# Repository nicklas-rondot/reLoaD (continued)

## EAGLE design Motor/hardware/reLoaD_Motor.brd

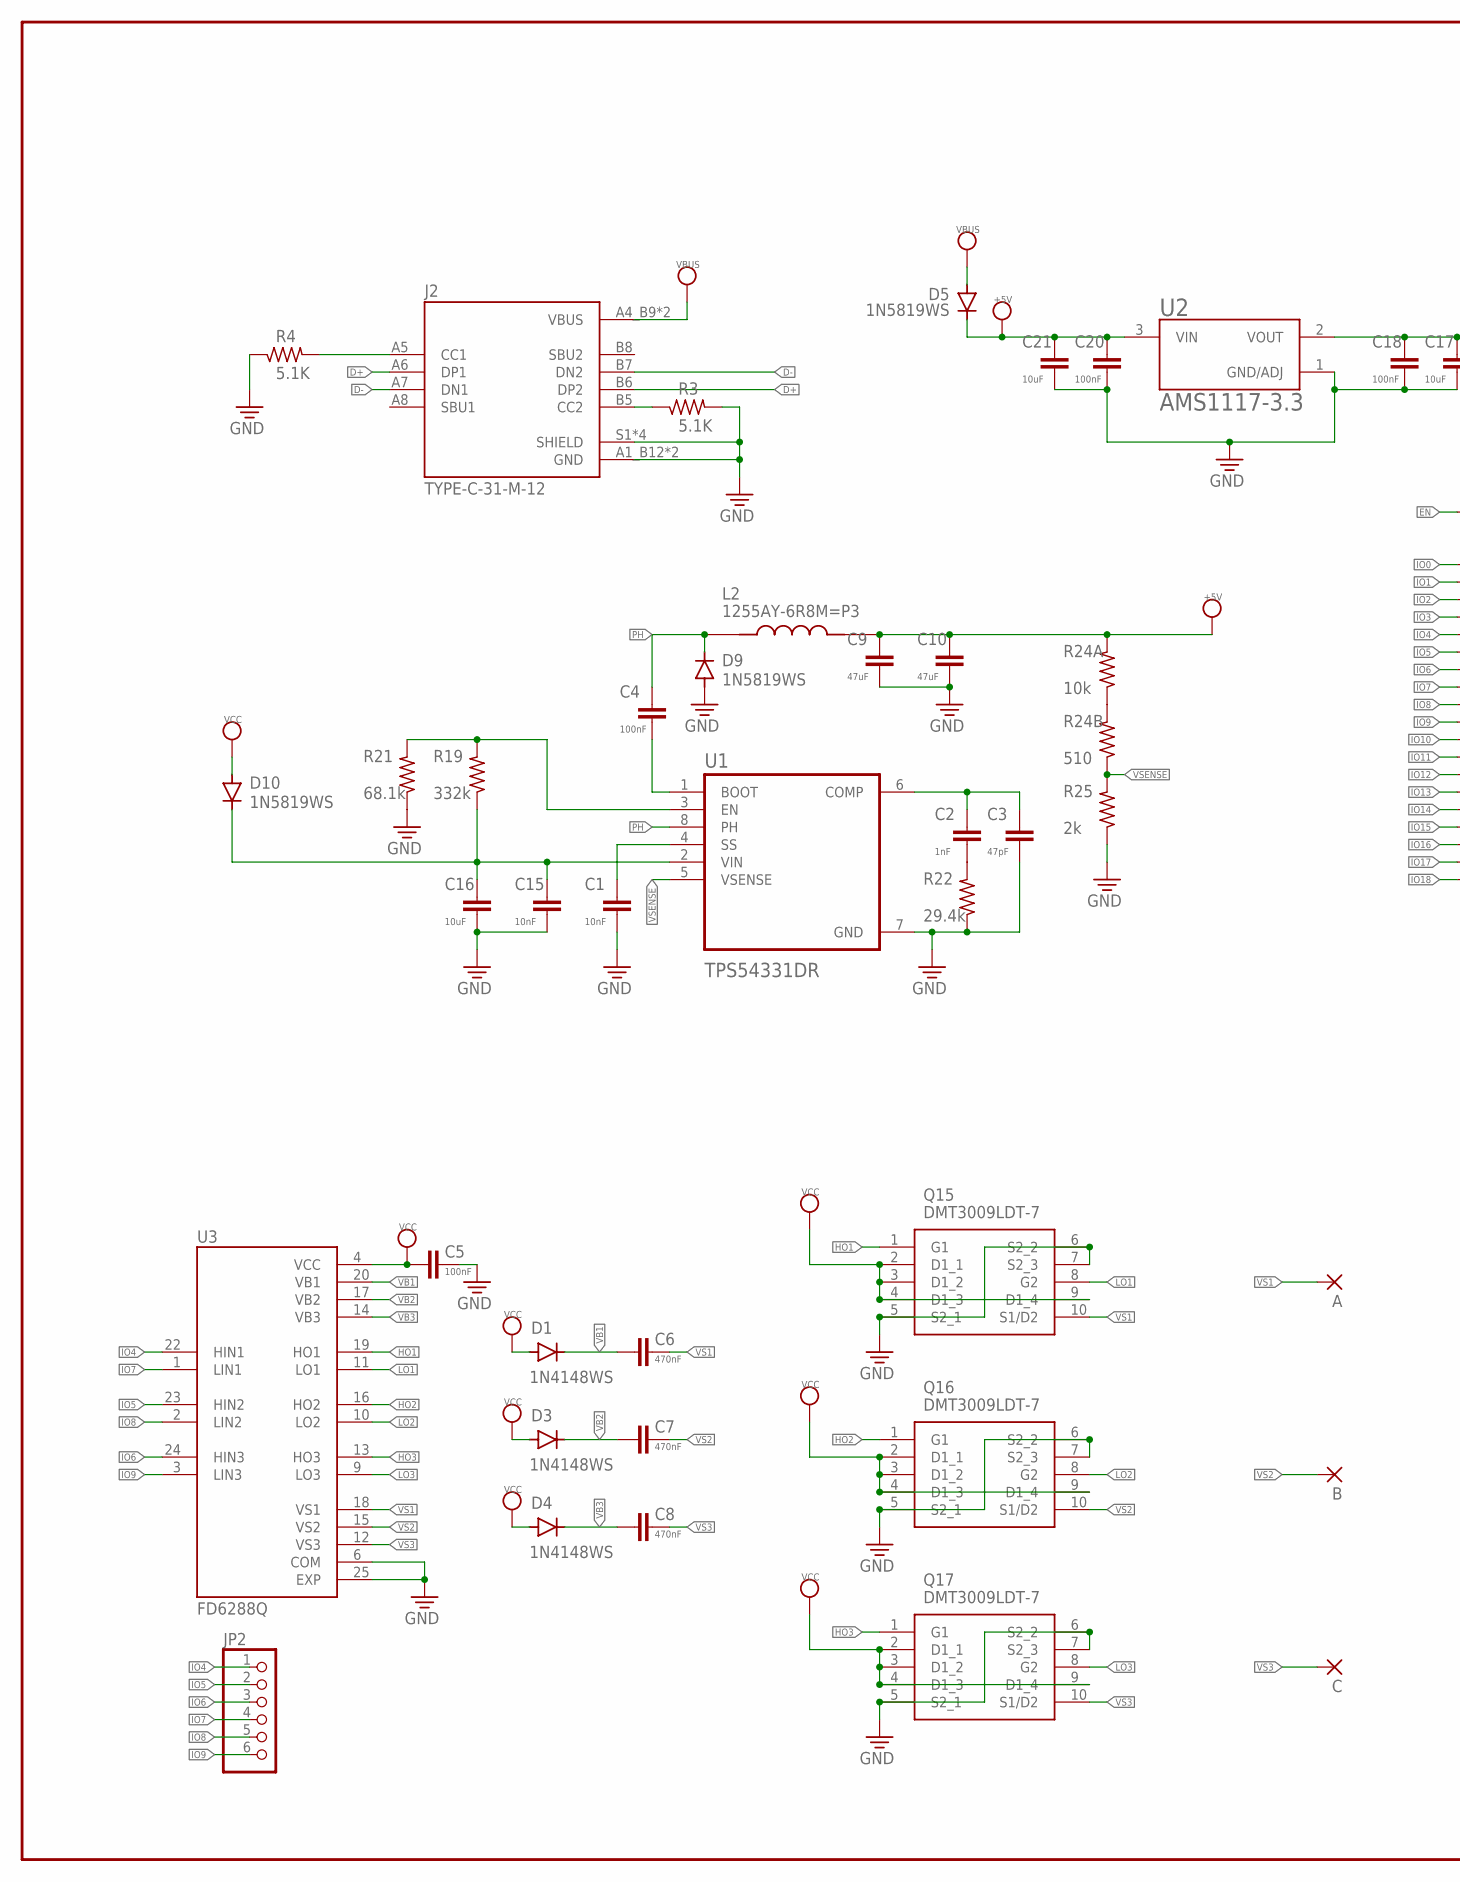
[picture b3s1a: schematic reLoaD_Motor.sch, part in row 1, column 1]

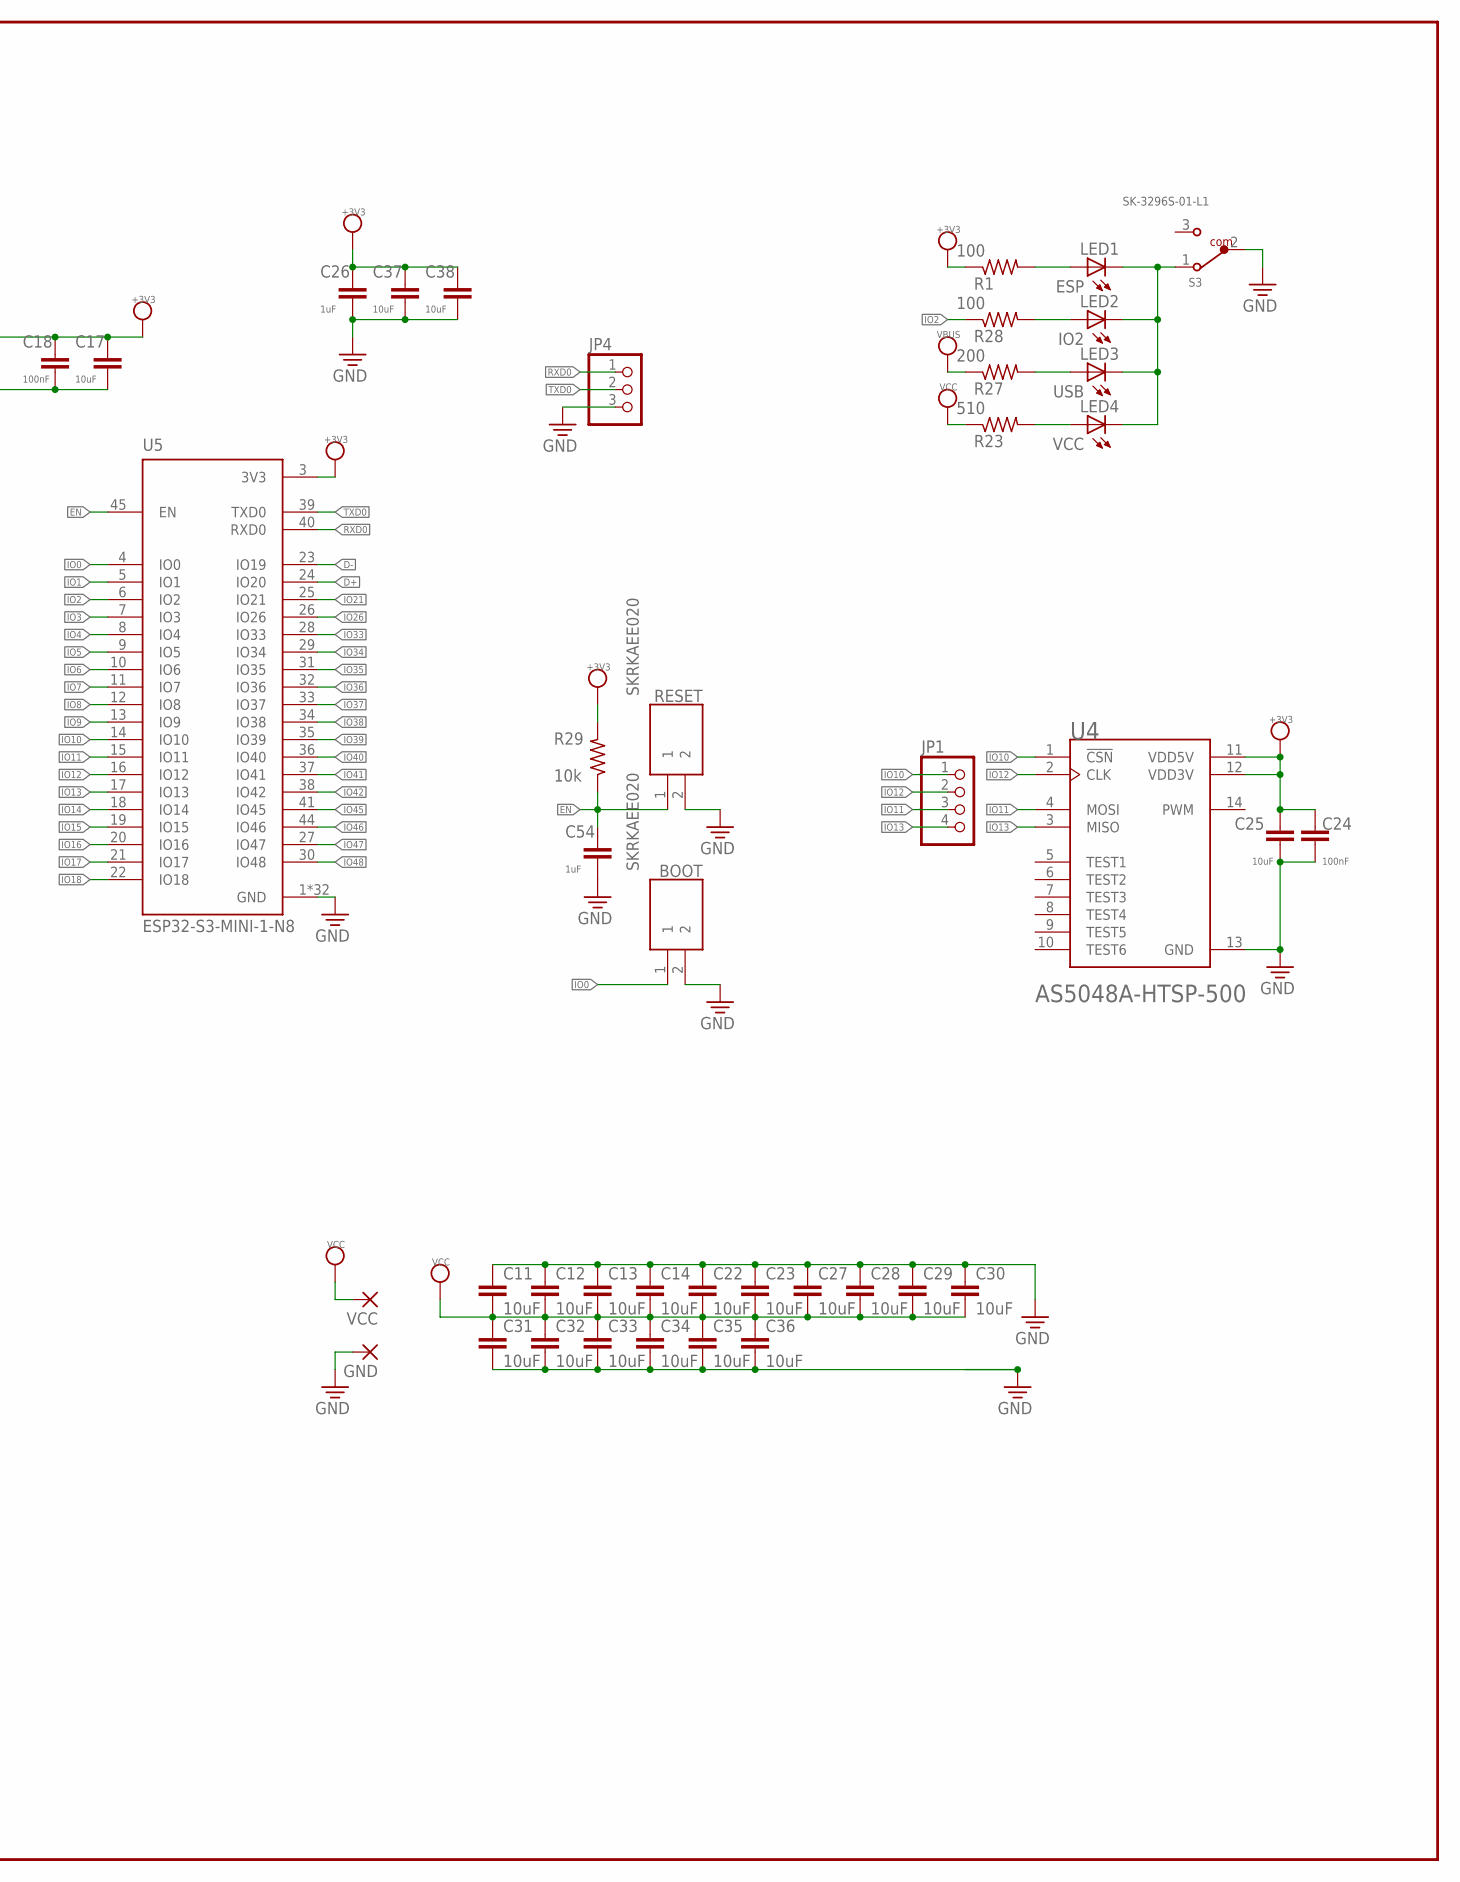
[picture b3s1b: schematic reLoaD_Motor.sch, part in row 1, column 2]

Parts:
A: 3,81/1,4
B: 3,81/1,4
BOOT: SKRKAEE020
C: 3,81/1,4
C1, C15: 10nF; C0603K
C2: 1nF; C0603K
C3: 47pF; C0603K
C4, C5, C18, C20, C24: 100nF; C0603K
C6, C7, C8: 470nF; C0603K
C9, C10: 47uF; C0603K
C11, C12, C13, C14, C22, C23, C27, C28, C29, C30, C31, C32, C33, C34, C35, C36: 10uF; C0805K
C16, C17, C21, C25, C37, C38: 10uF; C0603K
C26, C54: 1uF; C0603K
D1, D3, D4: 1N4148WS; SOD-323
D5, D9, D10: 1N5819WS; SOD323-W
GND: 3,81/1,4
J2: TYPE-C-31-M-12; HRO_TYPE-C-31-M-12
JP1: PINHD-1X4; 1X04
JP2: PINHD-1X6; 1X06
JP4: PINHD-1X3; 1X03
L2: 1255AY-6R8M=P3; IND_1255AY-6R8M=P3
LED1: ESP; CHIPLED_0805
LED2: IO2; CHIPLED_0805
LED3: USB; CHIPLED_0805
LED4: VCC; CHIPLED_0805
Q15, Q16, Q17: DMT3009LDT-7; DMT3009LDT7
R1, R28: 100; R0603
R3, R4: 5.1K; R0603
R19: 332k; R0603
R21: 68.1k; R0603
R22: 29.4k; R0603
R23, R24B: 510; R0603
R24A, R29: 10k; R0603
R25: 2k; R0603
R27: 200; R0603
RESET: SKRKAEE020
S3: SK-3296S-01-L1; 450404015514
U1: TPS54331DR; SOIC127P599X175-8N
U2: AMS1117-3.3; SOT229P700X180-4N
U3: FD6288Q; QFN50P400X400X90-25N
U4: AS5048A-HTSP-500; SOP65P640X120-14N
U5: ESP32-S3-MINI-1-N8; XCVR_ESP32-S3-MINI-1-N8
VCC: 3,81/1,4

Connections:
+3V3: C17.1, C18.1, C24.2, C25.2, C26.1, C37.1, C38.1, R1.1, R29.2, U2.2 (VOUT), U4.11 (VDD5V), U4.12 (VDD3V), U5.3 (3V3)
+5V: C9.1, C10.1, C20.1, C21.1, D5.C, L2.2, R24A.2, U2.3 (VIN)
D+: J2.A6 (DP1), J2.B6 (DP2), U5.24 (IO20)
D-: J2.A7 (DN1), J2.B7 (DN2), U5.23 (IO19)
EN: C54.1, R29.1, RESET.1, U5.45 (EN)
GND: BOOT.2, C1.2, C3.2, C5.1, C9.2, C10.2, C11.1, C12.1, C13.1, C14.1, C15.2, C16.2, C17.2, C18.2, C20.2, C21.2, C22.1, C23.1, C24.1, C25.1, C26.2, C27.1, C28.1, C29.1, C30.1, C31.2, C32.2, C33.2, C34.2, C35.2, C36.2, C37.2, C38.2, C54.2, D9.A, GND.1, J2.A1_B12 (GND), J2.B1_A12 (GND), J2.S1 (SHIELD), J2.S2 (SHIELD), J2.S3 (SHIELD), J2.S4 (SHIELD), JP4.3, Q15.5 (S2_1), Q15.6 (S2_2), Q15.7 (S2_3), Q16.5 (S2_1), Q16.6 (S2_2), Q16.7 (S2_3), Q17.5 (S2_1), Q17.6 (S2_2), Q17.7 (S2_3), R3.2, R4.1, R21.1, R22.1, R25.1, RESET.2, S3.2, U1.7 (GND), U2.1 (GND/ADJ), U3.6 (COM), U3.25 (EXP), U4.13 (GND), U5.1 (GND), U5.2 (GND), U5.42 (GND), U5.43 (GND), U5.46 (GND), U5.47 (GND), U5.48 (GND), U5.49 (GND), U5.50 (GND), U5.51 (GND), U5.52 (GND), U5.53 (GND), U5.54 (GND), U5.55 (GND), U5.56 (GND), U5.57 (GND), U5.58 (GND), U5.59 (GND), U5.60 (GND), U5.61 (GND), U5.61_1 (GND), U5.61_2 (GND), U5.61_3 (GND), U5.61_4 (GND), U5.61_5 (GND), U5.61_6 (GND), U5.61_7 (GND), U5.61_8 (GND), U5.62 (GND), U5.63 (GND), U5.64 (GND), U5.65 (GND)
HO1: Q15.1 (G1), U3.19 (HO1)
HO2: Q16.1 (G1), U3.16 (HO2)
HO3: Q17.1 (G1), U3.13 (HO3)
IO0: BOOT.1, U5.4 (IO0)
IO1: U5.5 (IO1)
IO2: R28.1, U5.6 (IO2)
IO3: U5.7 (IO3)
IO4: JP2.1, U3.22 (HIN1), U5.8 (IO4)
IO5: JP2.2, U3.23 (HIN2), U5.9 (IO5)
IO6: JP2.3, U3.24 (HIN3), U5.10 (IO6)
IO7: JP2.4, U3.1 (LIN1), U5.11 (IO7)
IO8: JP2.5, U3.2 (LIN2), U5.12 (IO8)
IO9: JP2.6, U3.3 (LIN3), U5.13 (IO9)
IO10: JP1.1, U4.1 (!CSN), U5.14 (IO10)
IO11: JP1.3, U4.4 (MOSI), U5.15 (IO11)
IO12: JP1.2, U4.2 (CLK), U5.16 (IO12)
IO13: JP1.4, U4.3 (MISO), U5.17 (IO13)
IO14: U5.18 (IO14)
IO15: U5.19 (IO15)
IO16: U5.20 (IO16)
IO17: U5.21 (IO17)
IO18: U5.22 (IO18)
IO21: U5.25 (IO21)
IO26: U5.26 (IO26)
IO33: U5.28 (IO33)
IO34: U5.29 (IO34)
IO35: U5.31 (IO35)
IO36: U5.32 (IO36)
IO37: U5.33 (IO37)
IO38: U5.34 (IO38)
IO39: U5.35 (IO39)
IO40: U5.36 (IO40)
IO41: U5.37 (IO41)
IO42: U5.38 (IO42)
IO45: U5.41 (IO45)
IO46: U5.44 (IO46)
IO47: U5.27 (IO47)
IO48: U5.30 (IO48)
LO1: Q15.8 (G2), U3.11 (LO1)
LO2: Q16.8 (G2), U3.10 (LO2)
LO3: Q17.8 (G2), U3.9 (LO3)
unnamed: LED3.A, R27.2
unnamed: LED4.A, R23.2
unnamed: LED1.A, R1.2
unnamed: J2.B5 (CC2), R3.1
unnamed: LED1.C, LED2.C, LED3.C, LED4.C, S3.1
unnamed: LED2.A, R28.2
unnamed: R19.2, R21.2, U1.3 (EN)
unnamed: C1.1, U1.4 (SS)
unnamed: R24A.1, R24B.2
unnamed: C2.1, C3.1, U1.6 (COMP)
unnamed: C2.2, R22.2
unnamed: C4.2, U1.1 (BOOT)
unnamed: C15.1, C16.1, D10.C, R19.1, U1.2 (VIN)
unnamed: J2.A5 (CC1), R4.2
PH: C4.1, D9.C, L2.1, U1.8 (PH)
RXD0: JP4.1, U5.40 (RXD0)
TXD0: JP4.2, U5.39 (TXD0)
VB1: C6.1, D1.C, U3.20 (VB1)
VB2: C7.1, D3.C, U3.17 (VB2)
VB3: C8.1, D4.C, U3.14 (VB3)
VBUS: D5.A, J2.A4_B9 (VBUS), J2.B4_A9 (VBUS), R27.1
VCC: C5.2, C11.2, C12.2, C13.2, C14.2, C22.2, C23.2, C27.2, C28.2, C29.2, C30.2, C31.1, C32.1, C33.1, C34.1, C35.1, C36.1, D1.A, D3.A, D4.A, D10.A, Q15.2 (D1_1), Q15.3 (D1_2), Q15.4 (D1_3), Q15.9 (D1_4), Q16.2 (D1_1), Q16.3 (D1_2), Q16.4 (D1_3), Q16.9 (D1_4), Q17.2 (D1_1), Q17.3 (D1_2), Q17.4 (D1_3), Q17.9 (D1_4), R23.1, U3.4 (VCC), VCC.1
VS1: A.1, C6.2, Q15.10 (S1/D2), U3.18 (VS1)
VS2: B.1, C7.2, Q16.10 (S1/D2), U3.15 (VS2)
VS3: C.1, C8.2, Q17.10 (S1/D2), U3.12 (VS3)
VSENSE: R24B.1, R25.2, U1.5 (VSENSE)

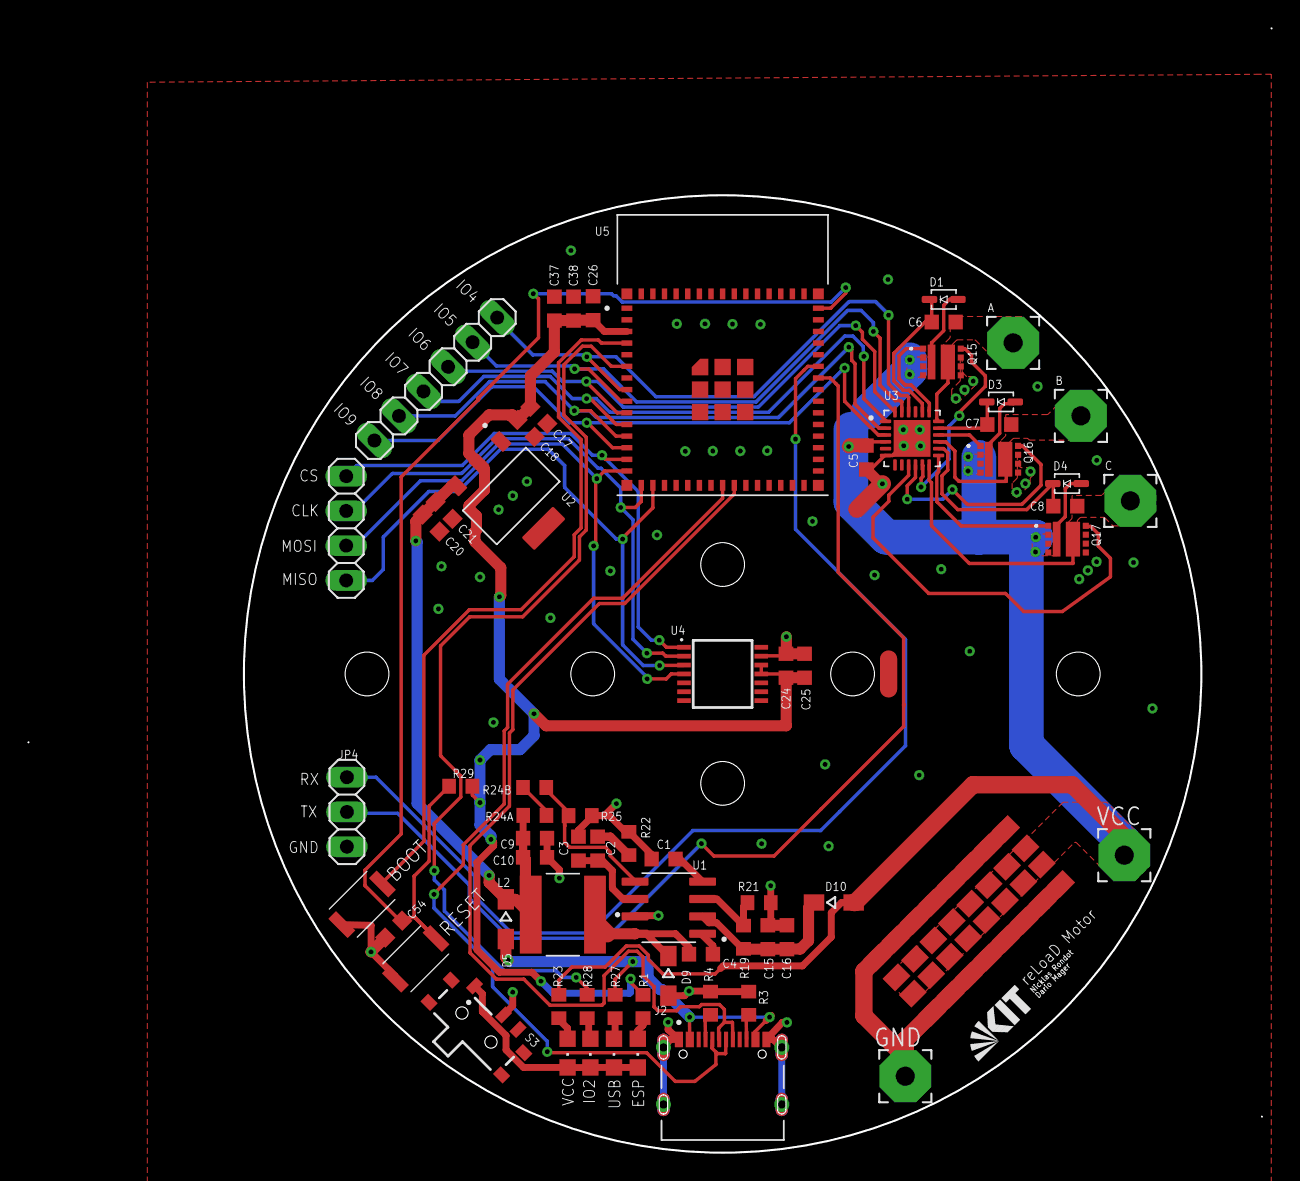
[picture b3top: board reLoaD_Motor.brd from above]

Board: 2 copper layers, 70.0 x 70.0 mm, 82 parts (0 on the bottom side), 50 nets.
